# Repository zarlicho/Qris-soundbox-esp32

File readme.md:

# QRIS Soundbox System - Complete Documentation

## Project Overview

QRIS Soundbox adalah sistem notifikasi pembayaran realtime yang dikembangkan untuk menerima dan memproses notifikasi pembayaran QRIS melalui protokol MQTT. Sistem ini mengintegrasikan payment gateway Midtrans dengan device soundbox melalui Adafruit server yang berfungsi sebagai webhook endpoint dan MQTT broker.

## PCB design

## System Architecture

### Core Components

1. **Payment Gateway**: Midtrans sebagai processor pembayaran QRIS
2. **Server Infrastructure**: Adafruit server dengan webhook endpoint dan MQTT broker
3. **QRIS Soundbox Device**: Device subscriber yang memberikan feedback audio dan visual
4. **Monitoring Dashboard**: Adafruit IO untuk monitoring dan logging

### Technology Stack

- **Payment Processing**: Midtrans Payment Gateway
- **Communication Protocol**: MQTT (Message Queuing Telemetry Transport)
- **Server Platform**: Adafruit IO
- **Device Communication**: MQTT Subscribe/Publish pattern
- **Data Format**: JSON for payment callback data

## System Flow Documentation

### 1. Payment Initiation Flow

**Customer Journey:**
- Customer melakukan scan QR code menggunakan mobile banking atau e-wallet
- Aplikasi mobile memproses pembayaran melalui sistem perbankan
- Data pembayaran diteruskan ke Midtrans payment gateway untuk processing

### 2. Payment Processing Flow

**Midtrans Processing:**
- Midtrans memvalidasi dan memproses transaksi pembayaran
- System menentukan status pembayaran (Success/Failed)
- Callback notification digenerate berdasarkan hasil processing

### 3. Webhook Callback Flow

**Server Side Processing:**
- Midtrans mengirim HTTP POST callback ke webhook endpoint Adafruit server
- Server menerima dan memvalidasi data callback
- Data callback diparse dan diverifikasi integritasnya
- Jika valid, data diproses untuk publikasi ke MQTT broker

**Data Validation Steps:**
- Signature verification untuk keamanan
- Transaction ID validation
- Amount dan merchant validation
- Timestamp verification

### 4. MQTT Publication Flow

**Message Broadcasting:**
- Validated payment data dipublikasi ke MQTT broker (Adafruit IO)
- Data dikirim ke specific topic: `qris/payment/notification`
- Message format menggunakan JSON structure
- QoS (Quality of Service) level ditentukan untuk reliability

**Sample MQTT Payload:**
```json
{
    "additionalInfo": {
        "issuerID": "93600821",
        "nettAmount": "9990.00",
        "payerName": "TEST",
        "payerPhoneNumber": "9360082112345678919",
        "paymentReferenceNo": "J0CP1INR2LOO",
        "posID": "A01",
        "retrievalReferenceNo": "1cqn60h00775",
        "totalRefund": "0.00"
    },
    "amount": {
        "currency": "IDR",
        "value": "10000.00"
    },
    "latestTransactionStatus": "00",
    "originalPartnerReferenceNo": "23545346"
}
```

### 5. Device Subscription Flow

**QRIS Soundbox Processing:**
- Device maintain persistent connection ke MQTT broker
- Subscribe ke topic `qris/payment/notification`
- Receive realtime notification ketika ada payment baru
- Parse JSON payload untuk extract payment information

### 6. User Feedback Flow

**Audio & Visual Feedback:**
- **Success Payment**: Play success sound + display transaction details
- **Failed Payment**: Play error sound + display failure message
- **Display Information**: Amount, transaction time, status, transaction ID
- **Logging**: Record transaction untuk audit trail

### 7. Monitoring & Analytics Flow

**Dashboard Integration:**
- Adafruit IO dashboard menampilkan realtime payment statistics
- Mobile app atau web interface untuk remote monitoring
- Transaction history dan analytics
- Device status monitoring (online/offline)

## Technical Implementation Details

### MQTT Configuration

**Broker Settings:**
- **Host**: io.adafruit.com
- **Port**: 1883 (non-SSL) atau 8883 (SSL)
- **Username**: Adafruit IO username
- **Key**: Adafruit IO key
- **Keep Alive**: 60 seconds
- **Clean Session**: True

### Webhook Endpoint Configuration

**Midtrans Webhook Setup:**
- **URL**: `https://io.adafruit.com/api/v2/webhooks/[webhook-key]`
- **Method**: POST
- **Content-Type**: application/json
- **Timeout**: 30 seconds
- **Retry**: 3 attempts dengan exponential backoff

### Error Handling Strategy

**Connection Resilience:**
- Auto-reconnect untuk MQTT connection
- Offline message queuing
- Retry mechanism untuk failed callbacks
- Graceful degradation ketika server unavailable

**Data Integrity:**
- Duplicate transaction detection
- Checksum verification
- Transaction sequence validation
- Timeout handling untuk stuck transactions

### Security Considerations

**Data Protection:**
- HTTPS untuk webhook communications
- MQTT over SSL/TLS
- Signature validation dari Midtrans
- API key rotation policy
- Access control untuk MQTT topics

**Privacy Compliance:**
- Customer data anonymization
- PCI DSS compliance untuk payment data
- Log data retention policy
- Secure storage untuk transaction records

## Deployment Architecture

### Production Environment

**Infrastructure Requirements:**
- Reliable internet connection untuk device
- Backup power supply untuk continuous operation
- Local storage untuk offline transaction queuing
- Audio output system untuk sound notifications

**Scalability Considerations:**
- Multiple device support dengan unique client IDs
- Load balancing untuk high-volume transactions
- Database optimization untuk transaction storage
- Caching strategy untuk frequent queries

---

## System Flow Diagram

```mermaid
flowchart TD
    A[Customer] --> B[Scan QR Code]
    B --> C[Mobile Banking/E-Wallet App]
    C --> D[Payment Processing]
    D --> E[Midtrans Payment Gateway]
    
    E --> F{Payment Status}
    F -->|Success| G[Payment Callback]
    F -->|Failed| H[Failed Callback]
    
    G --> I[Webhook Endpoint<br/>Adafruit Server]
    H --> I
    
    I --> J[Process Callback Data]
    J --> K[Validate Payment Data]
    K --> L{Data Valid?}
    
    L -->|Yes| M[Publish to MQTT Broker<br/>Adafruit IO]
    L -->|No| N[Log Error & Reject]
    
    M --> O[MQTT Topic<br/>qris/payment/notification]
    
    O --> P[QRIS Soundbox Device<br/>MQTT Subscriber]
    P --> Q[Receive Payment Data]
    Q --> R[Parse JSON Data]
    R --> S[Extract Payment Info<br/>Amount, Status, Transaction ID]
    
    S --> T{Payment Success?}
    T -->|Yes| U[Play Success Sound]
    T -->|Failed| V[Play Failed Sound]
    
    U --> W[Display Transaction Info<br/>Amount, Time, Status]
    V --> W
    
    W --> X[Log Transaction]
    X --> Y[Ready for Next Payment]
    
    %% Additional Components
    Z[Adafruit IO Dashboard] --> O
    AA[Mobile App/Web Monitor] --> Z
    
    %% Styling
    classDef customer fill:#e1f5fe
    classDef payment fill:#f3e5f5
    classDef server fill:#e8f5e8
    classDef device fill:#fff3e0
    classDef data fill:#fce4ec
    
    class A,B,C customer
    class D,E,F,G,H payment
    class I,J,K,L,M,O,Z server
    class P,Q,R,S,T,U,V,W,X,Y device
    class AA data
```

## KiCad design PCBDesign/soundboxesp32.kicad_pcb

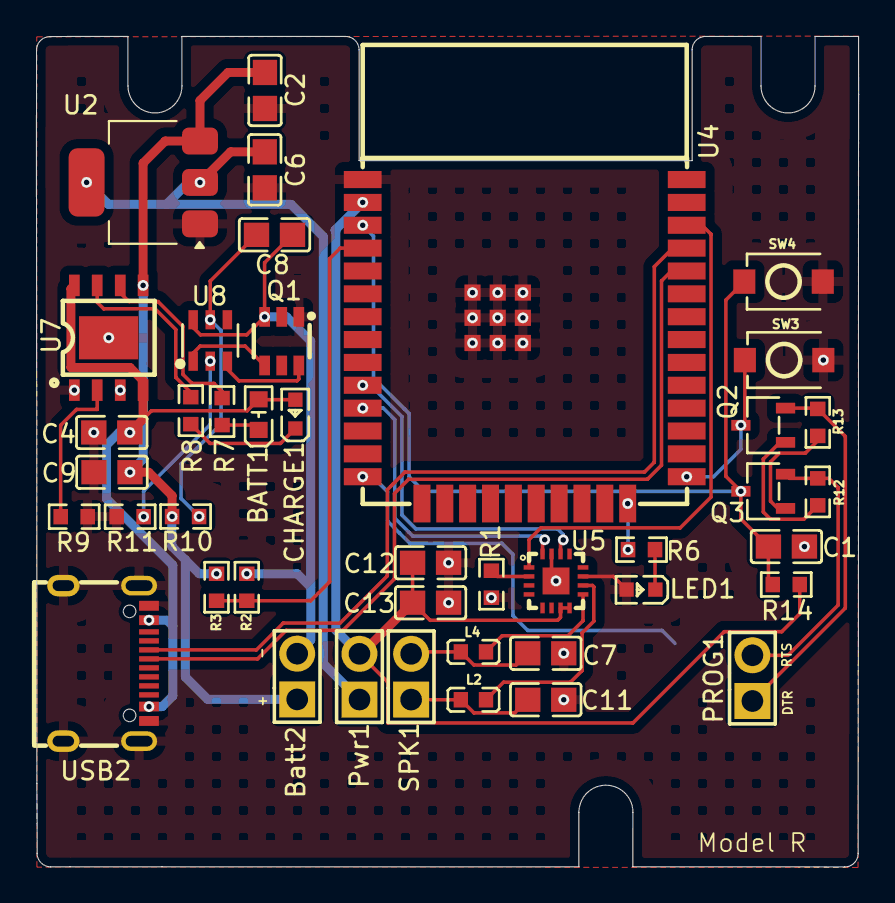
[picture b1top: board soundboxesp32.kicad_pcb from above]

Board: 2 copper layers, 45.7 x 46.1 mm, 43 parts (1 on the bottom side), 35 nets.

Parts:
BATT1: A-SP192DGHC-C01-4T; LED0603-FD
Batt2: ZX-PZ2.54-1-2PZZ; HDR-TH_2P-P2.54-V-M
C1, C4, C8, C12: 100nF; C0805
C2, C6: 22uF; C0805
C7, C11: 220pF; C0805
C9, C13: 10uF; C0805
CHARGE1: XL-1608SURC-06; LED0603-RD_RED
L2, L4: 330Ω; L0603
LED1: XL-1608SURC-06; LED0603-RD_RED
PROG1: ZX-PZ2.54-1-2PZZ; HDR-TH_2P-P2.54-V-M
Pwr1: ZX-PZ2.54-1-2PZZ; HDR-TH_2P-P2.54-V-M
Q1: FS8205; SOT-23-6_L2.9-W1.6-P0.95-LS2.8-BR
Q2, Q3: MMBT3904LT1G; SOT-23-3_L2.9-W1.6-P1.90-LS2.8-BR
R1, R3: RC0603FR-07100KL; R0603
R2: FRC0603F3003TS; R0603
R6, R7, R8, R9, R11: 1K; R0603
R10: 100Ω; R0603
R12, R13, R14: 10K; R0603
SPK1: ZX-PZ2.54-1-2PZZ; HDR-TH_2P-P2.54-V-M
SW1, SW3, SW4: TS-1088-AR02016; SW-SMD_L3.9-W3.0-P4.45
U2: AMS1117-3.3; SOT-223-3_TabPin2
U4: ESP32-WROOM-32E(4MB); WIFI-SMD_ESP32-WROOM-32E
U5: MAX98357AETE+T; TQFN-16_L3.0-W3.0-P0.50-BL-EP1.5
U7: TP4056; ESOP-8_L4.9-W3.9-P1.27-LS6.0-BL-EP
U8: DW01A_C2927799; SOT-23-6_L2.9-W1.6-P0.95-LS2.8-BL
USB2: TYPE-C 16PIN 2MD(073); USB-C-SMD_TYPE-C-6PIN-2MD-073

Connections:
+3.3V: C12.1, C13.1, Pwr1.2, R14.2, U4.2 (3V3), U5.7 (VDD), U5.8 (VDD)
+5V: BATT1.1 (A), C4.1, CHARGE1.2 (A), U7.4 (VCC), U7.8 (CE), USB2.2 (VBUS), USB2.11 (VBUS)
+BATT: Batt2.1, C2.2, C9.1, R3.2, R10.2, U2.3 (VI), U7.5 (BAT)
BCLK: U4.11 (IO26), U5.16 (BCLK)
DIN: U4.36 (IO22), U5.1 (DIN)
DTR: PROG1.1, Q2.2, R13.1
GND: C1.2, C2.1, C4.2, C6.1, C7.1, C9.2, C11.1, C12.2, C13.2, LED1.2 (A), Q1.1 (S1), R1.1, R9.2, R11.1, SW1.2, SW3.2, SW4.2, U2.1 (GND), U4.1 (GND), U4.39 (GND), U5.11 (GND), U5.15 (GND), U5.17 (EP), U7.1 (TEMP), U7.3 (GND), U7.9 (EP), USB2.1 (GND), USB2.12 (GND), USB2.13 (SHELL), USB2.14 (SHELL)
GPIO0: Q2.3, SW3.1, U4.25 (IO0)
IO12: SW1.1, U4.14 (IO12)
LRC: U4.10 (IO25), U5.14 (LRCLK)
unnamed: BATT1.2 (K), R7.2
unnamed: C7.2, L4.2, SPK1.2
unnamed: C11.2, L2.2, SPK1.1
unnamed: CHARGE1.1 (K), R8.2
unnamed: LED1.1 (K), R6.2
unnamed: Q1.6 (G1), U8.3 (OC)
unnamed: Q1.4 (G2), U8.1 (OD)
unnamed: Batt2.2, C8.2, Q1.3 (S2), R2.1, U8.6 (VSS)
unnamed: Q2.1, R12.2
unnamed: Q3.1, R13.2
unnamed: C6.2, Pwr1.1, U2.2 (VO)
unnamed: R6.1, U4.24 (IO2)
unnamed: R1.2, U5.2 (GAIN_SLOT)
unnamed: L2.1, U5.10 (OUTN)
unnamed: L4.1, U5.9 (OUTP)
unnamed: R9.1, U7.2 (PROG)
unnamed: R8.1, U7.7 (~CHRG)
unnamed: R7.1, U7.6 (~STDBY)
unnamed: R11.2, U8.2 (CSI)
unnamed: C8.1, R10.1, U8.5 (VDD)
RESET: C1.1, Q3.3, R14.1, SW4.1, U4.3 (EN)
RTS: PROG1.2, Q3.2, R12.1
RX: U4.34 (RXD0), USB2.6 (DP1), USB2.8 (DP2)
SENSOR_VP: R2.2, R3.1, U4.4 (SENSOR_VP)
TX: U4.35 (TXD0), USB2.5 (DN2), USB2.7 (DN1)

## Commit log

2026-05-17 first
